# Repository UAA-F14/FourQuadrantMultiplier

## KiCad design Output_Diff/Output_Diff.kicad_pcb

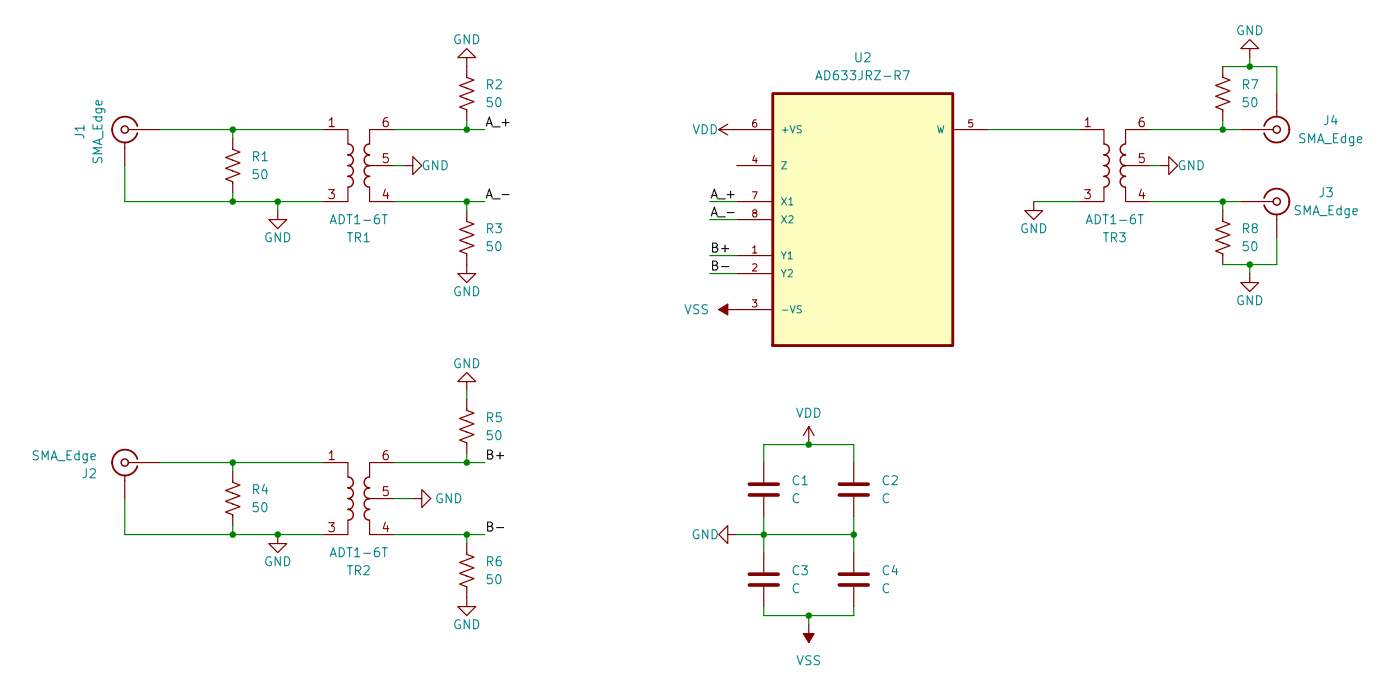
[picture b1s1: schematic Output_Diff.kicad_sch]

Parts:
C1, C2, C3, C4: C; C_0603_1608Metric
J1, J2, J3, J4: SMA_Edge; SMA_Molex_73251-1153_EdgeMount_Horizontal
R1, R2, R3, R4, R5, R6, R7, R8: 50; R_0603_1608Metric
TR1, TR2, TR3: ADT1-6T; Mini-Circuits_CD637_H5.23mm
U2: AD633JRZ-R7; SOIC127P600X175-8N; MPN AD633

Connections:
/A_+: R2.2, TR1.6, U2.7 (X1)
/A_-: R3.1, TR1.4, U2.8 (X2)
/B+: R5.2, TR2.6, U2.1 (Y1)
/B-: R6.1, TR2.4, U2.2 (Y2)
GND: C1.2, C2.2, C3.1, C4.1, J1.2 (Ext), J2.2 (Ext), J3.2 (Ext), J4.2 (Ext), R1.2, R2.1, R3.2, R4.2, R5.1, R6.2, R7.1, R8.2, TR1.3, TR1.5, TR2.3, TR2.5, TR3.3, TR3.5
unnamed: J1.1 (In), R1.1, TR1.1
unnamed: J2.1 (In), R4.1, TR2.1
unnamed: J3.1 (In), R8.1, TR3.4
unnamed: J4.1 (In), R7.2, TR3.6
unnamed: TR3.1, U2.5 (W)
VDD: C1.1, C2.1, U2.6 (+VS)
VSS: C3.2, C4.2, U2.3 (-VS)

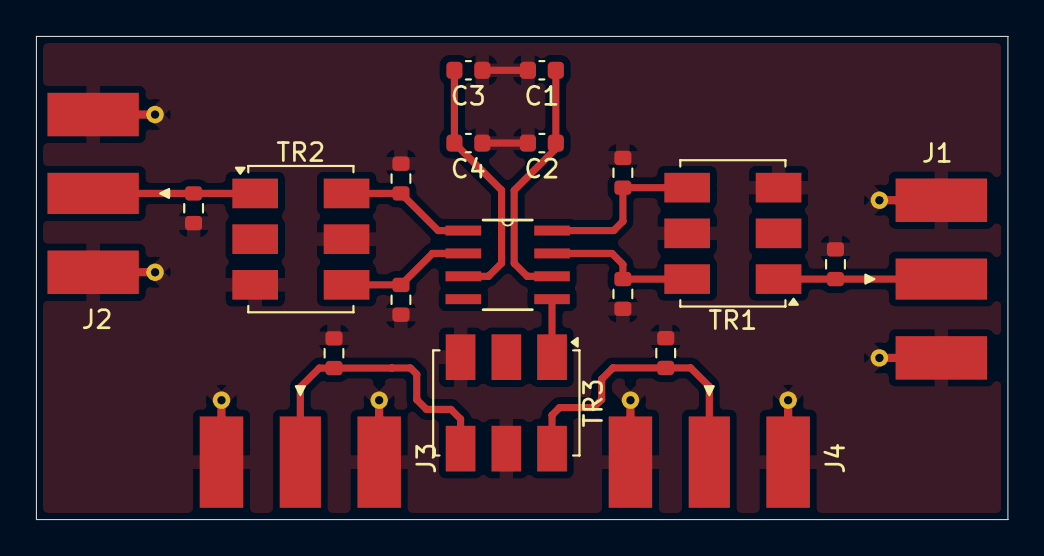
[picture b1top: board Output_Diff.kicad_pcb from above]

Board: 2 copper layers, 54.0 x 26.8 mm, 20 parts (0 on the bottom side), 12 nets.

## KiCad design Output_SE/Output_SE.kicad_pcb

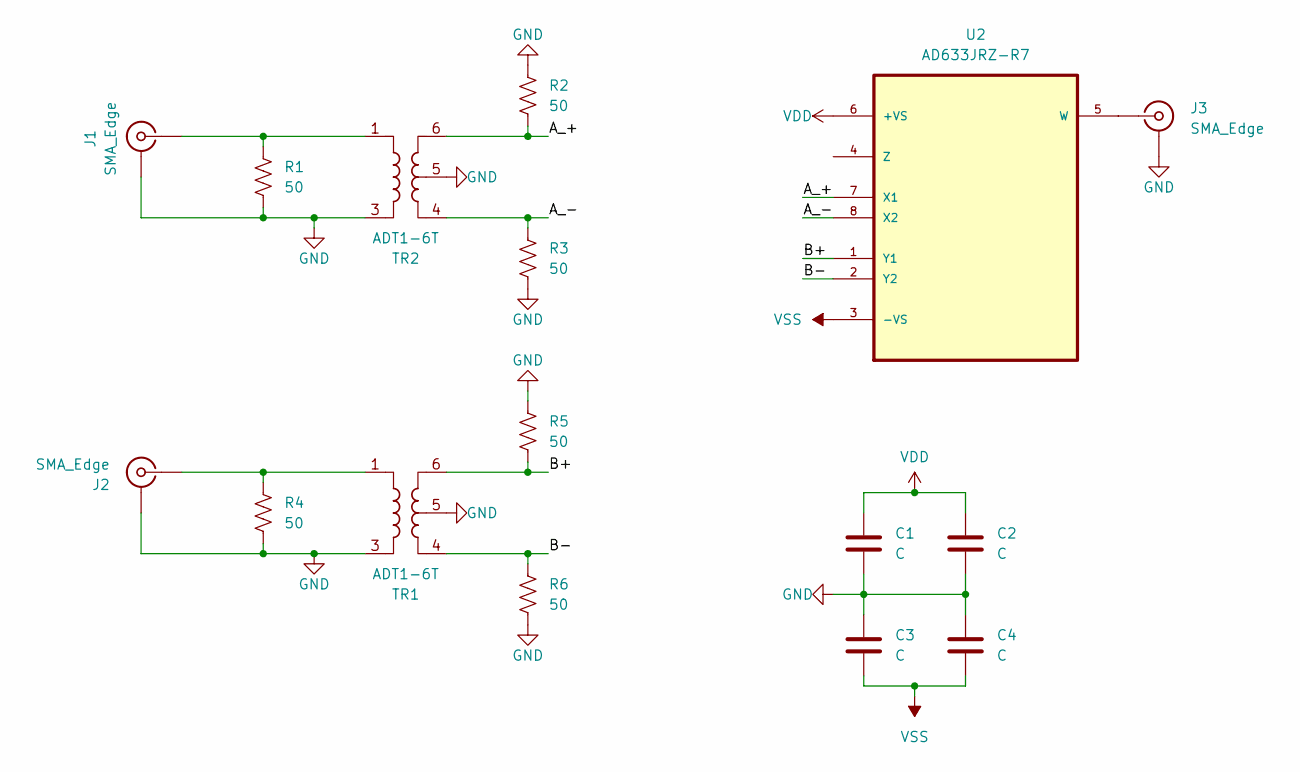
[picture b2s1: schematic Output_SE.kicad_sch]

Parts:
C1, C2, C3, C4: C; C_0603_1608Metric
J1, J2, J3: SMA_Edge; SMA_Molex_73251-1153_EdgeMount_Horizontal
R1, R2, R3, R4, R5, R6: 50; R_0603_1608Metric
TR1, TR2: ADT1-6T; Mini-Circuits_CD637_H5.23mm
U2: AD633JRZ-R7; SOIC127P600X175-8N; MPN AD633

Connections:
/A_+: R2.2, TR2.6, U2.7 (X1)
/A_-: R3.1, TR2.4, U2.8 (X2)
/B+: R5.2, TR1.6, U2.1 (Y1)
/B-: R6.1, TR1.4, U2.2 (Y2)
GND: C1.2, C2.2, C3.1, C4.1, J1.2 (Ext), J2.2 (Ext), J3.2 (Ext), R1.2, R2.1, R3.2, R4.2, R5.1, R6.2, TR1.3, TR1.5, TR2.3, TR2.5
unnamed: J1.1 (In), R1.1, TR2.1
unnamed: J2.1 (In), R4.1, TR1.1
unnamed: J3.1 (In), U2.5 (W)
VDD: C1.1, C2.1, U2.6 (+VS)
VSS: C3.2, C4.2, U2.3 (-VS)

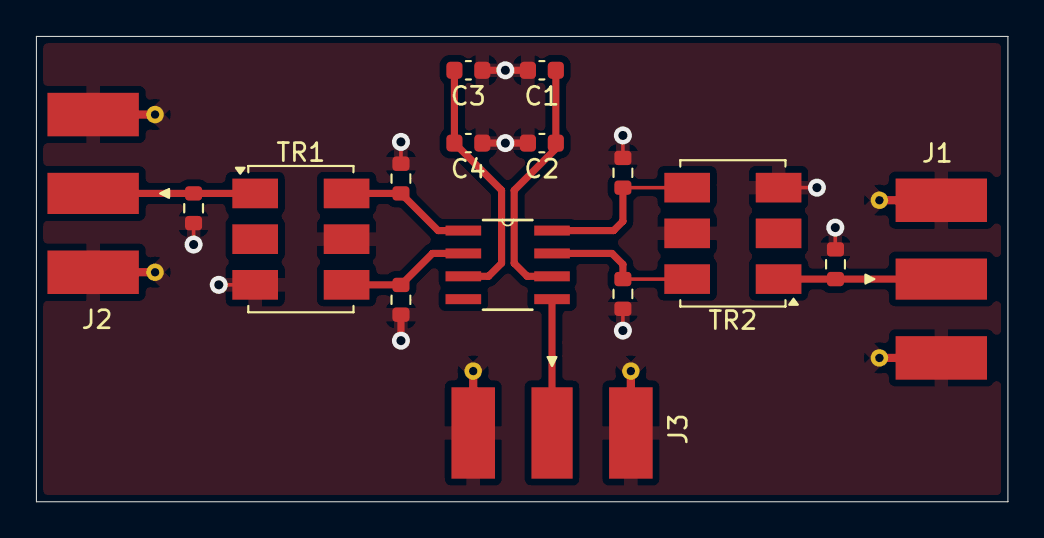
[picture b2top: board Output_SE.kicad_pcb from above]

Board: 2 copper layers, 54.0 x 25.9 mm, 16 parts (0 on the bottom side), 10 nets.
